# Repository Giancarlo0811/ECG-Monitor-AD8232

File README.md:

# ECG-Monitor-AD8232
Diseño de Monitor ECG (Electrocardiograma) de una sola derivación (Single Lead) basado en el AFE TI AD8232.

## 📚 Proyecto Académico
*Proyecto desarrollado como parte de la asignatura ***EC3083 Taller de Equipos Electrónicos*** en la Universidad Simón Bolívar.*

**Objetivo**: Diseñar un circuito ECG con esquemático y PCB layout.

## 🛠️ Detalles Técnicos
- **Herramientas**:
    - **Proteus**: Esquemático, simulación y PCB.
    - **KiCad**: Esquemático y PCB.
- **Características clave**:
    - **Analog Front End (AFE)**: TI AD8232.
    - **Acondicionamiento de señal**: filtro pasabanda 0.445-43.6 Hz (simulado en Proteus).
    - **Ganancia media banda**: 59.1 dB (simulado en Proteus).
    - **Diseño PCB**: 2-layer layout.
    - **Bill of Materials (BOM)**: Lista de componentes completa con costos.

## 📸 Esquemático + PCB

### Proteus

### KiCad

## 📊 Simulación

### 📈 Bode de amplitud y fase de la ganancia modo diferencial

Caso pasa bajo: fc = 43.6 Hz

Caso pasa alto: fc = 0.445 Hz

Avd = 59,1 dB frecuencias medias

### 📈 Vid (ECG simulado 0.625 mVp) y Vo (OUT)

## 📋 BOM (Bill of Materials)
[Descargar BOM](./Documentos/BOM_Monitor_ECG_AFE_AD8232.xlsx)

## 📂 Documentación completa
Para una documentación más detallada descargar:
[Presentación PDF](/Documentos/Presentacion_ECG_Monitor_AFE_AD8232.pdf)

## ⚠️ Disclaimer
Esto es un diseño teórico. La fabricación de la PCB y sus pruebas están pendientes.

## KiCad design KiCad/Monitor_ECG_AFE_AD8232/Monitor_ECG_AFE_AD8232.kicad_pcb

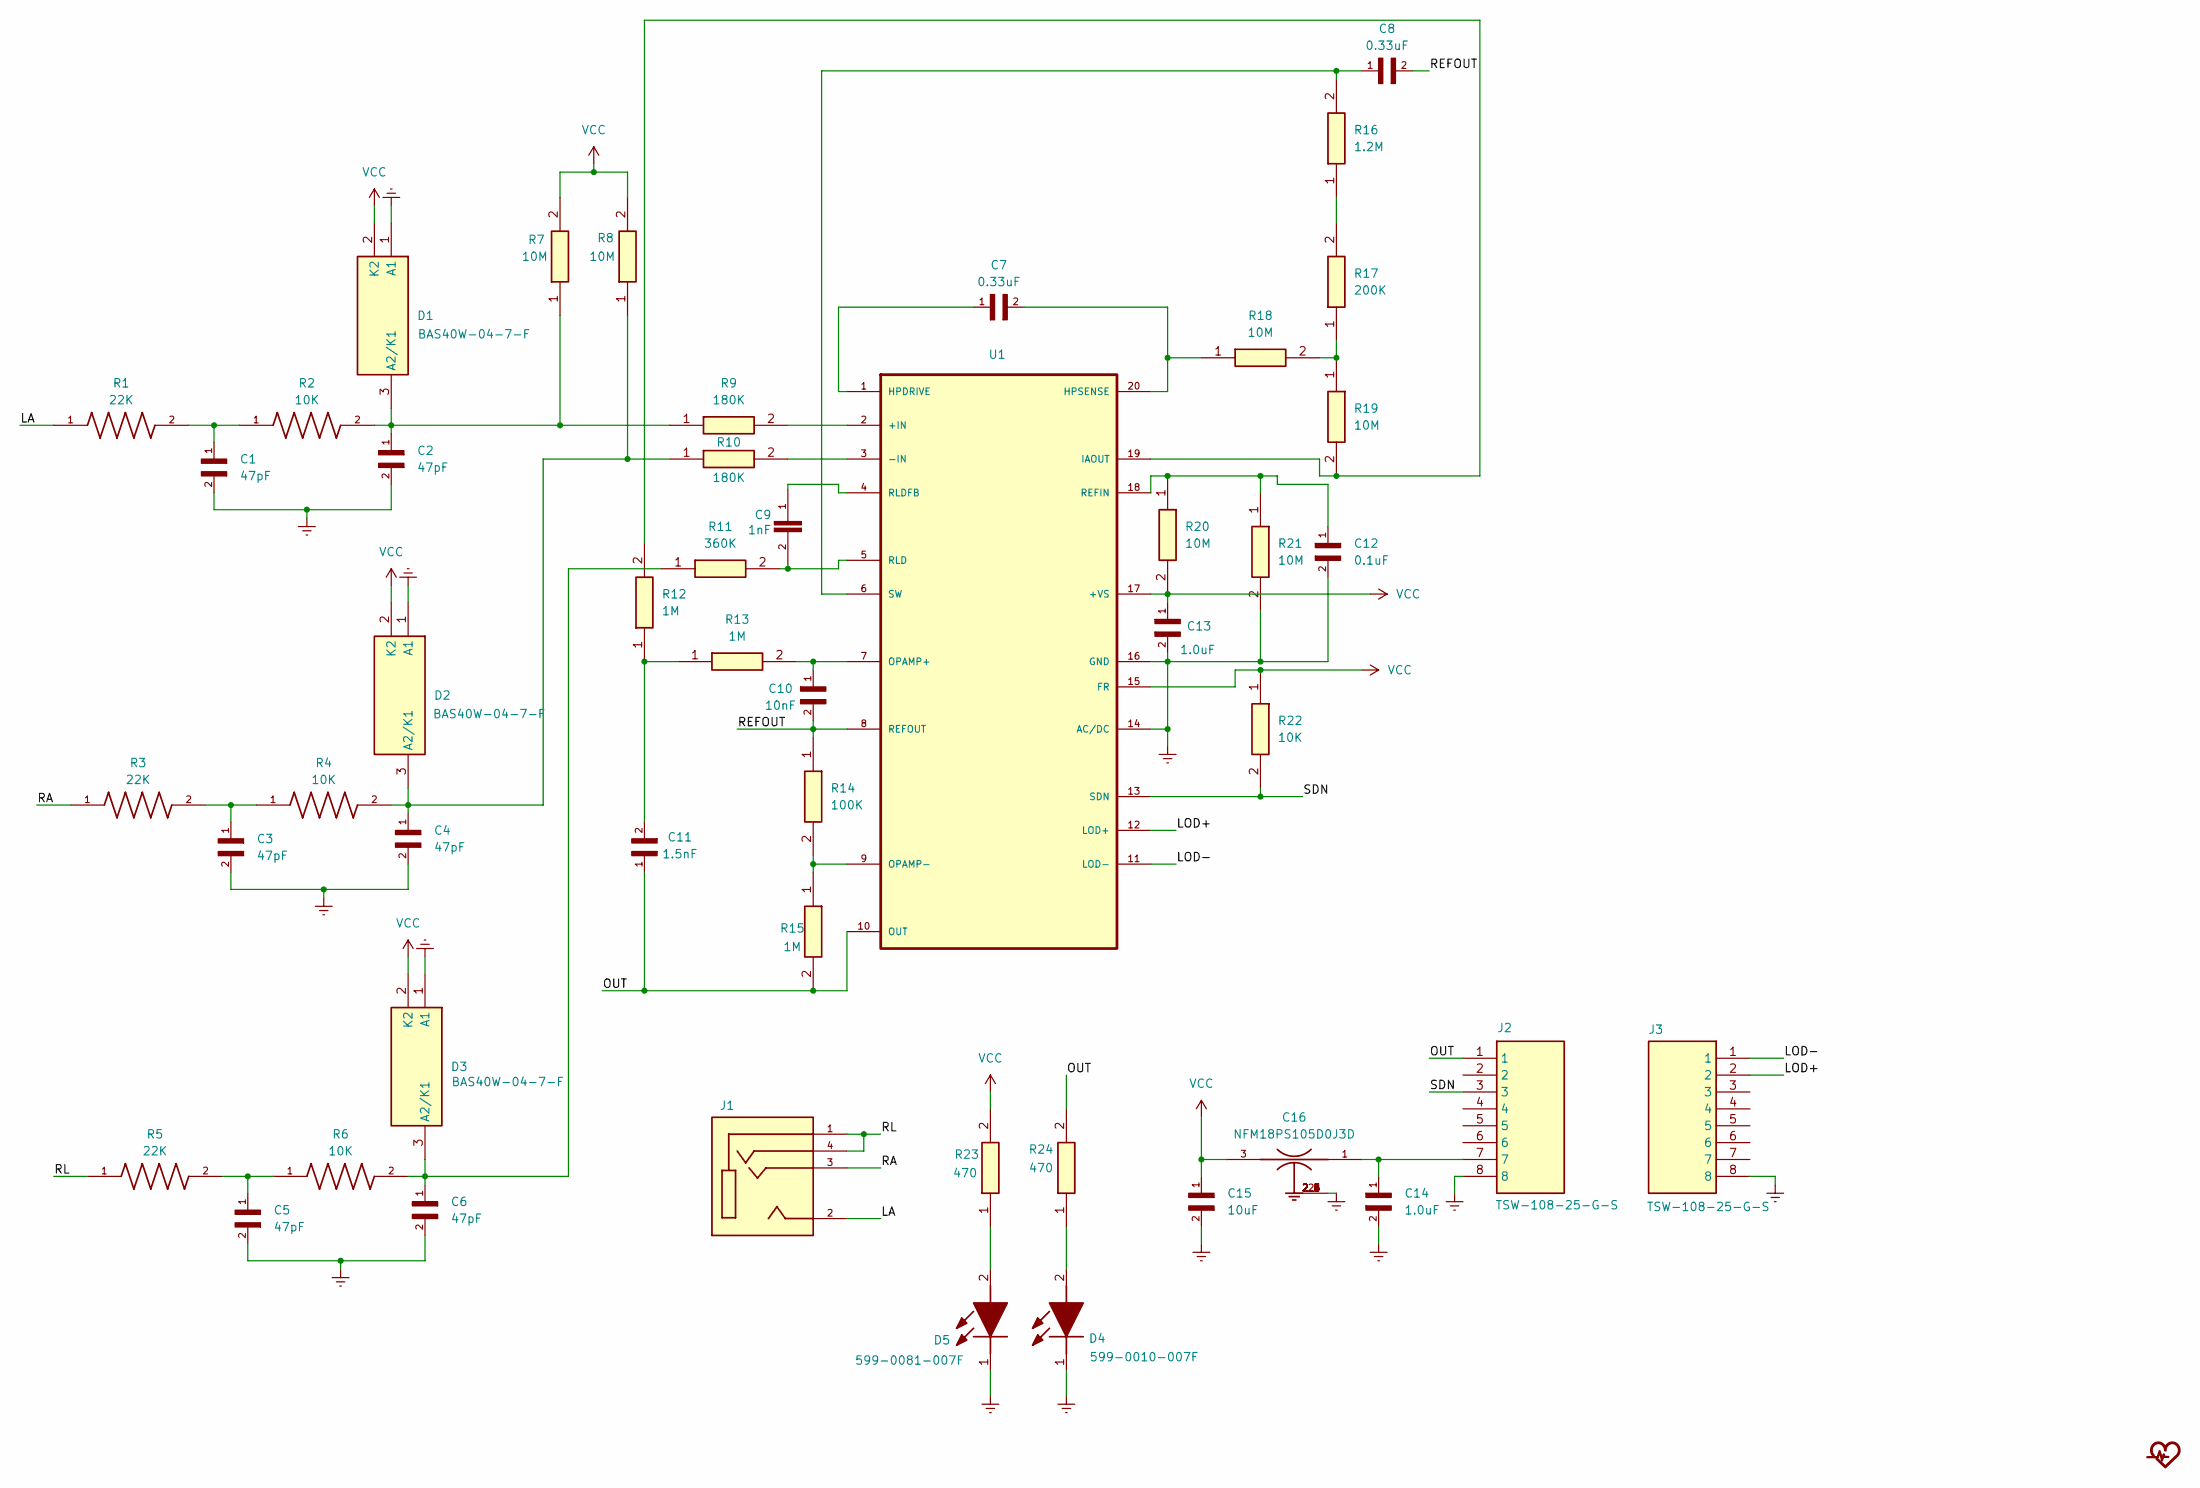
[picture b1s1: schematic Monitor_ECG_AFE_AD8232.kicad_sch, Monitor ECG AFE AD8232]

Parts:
C1, C2, C3, C4, C5, C6: 47pF; CAPC1608X90
C7, C8: 0.33uF; CAPC1608X87N
C9: 1nF; CAPC1608X90
C10: 10nF; CAPC1608X90
C11: 1.5nF; CAPC1608X90
C12: 0.1uF; CAPC1608X90N
C13, C14: 1.0uF; CAPC1608X90N
C15: 10uF; CAPC1608X90N
C16: NFM18PS105D0J3D; FIL_NFM18PS105D0J3D
D1, D2, D3: BAS40W-04-7-F; SOT65P222X110-3N; Manufacturer_Part_Number BAS40W-04-7-F; Mouser Part Number 621-BAS40W-04-F
D4: 599-0010-007F; LEDM168X70N; Manufacturer_Part_Number 599-0010-007F; Mouser Part Number 645-599-0010-007F
D5: 599-0081-007F; CAPC1608X95; Manufacturer_Part_Number 599-0081-007F; Mouser Part Number 645-599-0081-007F
ECG_logo1: LOGO; logo_5x5
J1: SJ-43514-SMT-TR; CUI_SJ-43514-SMT-TR; PARTREV 1.05
J2, J3: TSW-108-25-G-S; TSW-108-XX-YY-S; Manufacturer_Part_Number TSW-108-25-G-S; Mouser Part Number 200-TSW10825GS
R1, R3, R5: 22K; RESC1608X55N
R2, R4, R6: 10K; RES_ERJ-3GEYJ103V; PARTREV 3/1/2020
R7, R8, R18, R19, R20, R21: 10M; RESC1608X55N; Manufacturer_Part_Number ERJ-3GEYJ106V; Mouser Part Number 667-ERJ-3GEYJ106V
R9, R10: 180K; RESC1608X55N; Manufacturer_Part_Number RC0603JR-07180KL; Mouser Part Number 603-RC0603JR-07180KL
R11: 360K; RESC1608X55N; Manufacturer_Part_Number RC0603FR-07360KL; Mouser Part Number 603-RC0603FR-07360KL
R12, R13, R15: 1M; RESC1608X55N; Manufacturer_Part_Number ERJ-3GEYJ105V; Mouser Part Number 667-ERJ-3GEYJ105V
R14: 100K; RESC1608X55N; Manufacturer_Part_Number ERJ-3EKF1003V; Mouser Part Number 667-ERJ-3EKF1003V
R16: 1.2M; RESC1608X55N; Manufacturer_Part_Number ERJ-3GEYJ125V; Mouser Part Number 667-ERJ-3GEYJ125V
R17: 200K; RESC1608X55N; Manufacturer_Part_Number RC0603JR-07200KL; Mouser Part Number 603-RC0603JR-07200KL
R22: 10K; RESC1608X55N; Manufacturer_Part_Number ERJ-3EKF1002V; Mouser Part Number 667-ERJ-3EKF1002V
R23, R24: 470; RESC1608X55N; Manufacturer_Part_Number RC0603JR-07470RL; Mouser Part Number 603-RC0603JR-07470RL
U1: AD8232ACPZ-R7; QFN50P400X400X100-21N

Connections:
/LA: J1.2, R1.1
/LOD+: J3.2, U1.12 (LOD+)
/LOD-: J3.1, U1.11 (LOD-)
/OUT: C11.1, J2.1, R15.2, R24.2, U1.10 (OUT)
/RA: J1.3, R3.1
/REFOUT: C8.2, C10.2, R14.1, U1.8 (REFOUT)
/RL: J1.1, J1.4, R5.1
/SDN: J2.3, R22.2, U1.13 (SDN)
Earth: C1.2, C2.2, C3.2, C4.2, C5.2, C6.2, C12.2, C13.2, C14.2, C15.2, C16.2, C16.2_1, C16.2_2, C16.2_3, C16.2_4, C16.2_5, C16.2_6, D1.1 (A1), D2.1 (A1), D3.1 (A1), D4.1 (K), D5.1 (K), J2.8, J3.8, R21.2, U1.14 (AC/DC), U1.16 (GND)
unnamed: C1.1, R1.2, R2.1
unnamed: C3.1, R3.2, R4.1
unnamed: C5.1, R5.2, R6.1
unnamed: C11.2, R12.1, R13.1
unnamed: C14.1, C16.1, J2.7
unnamed: C2.1, D1.3 (A2/K1), R2.2, R7.1, R9.1
unnamed: C4.1, D2.3 (A2/K1), R4.2, R8.1, R10.1
unnamed: C6.1, D3.3 (A2/K1), R6.2, R11.1
unnamed: D4.2 (A), R24.1
unnamed: D5.2 (A), R23.1
unnamed: R16.1, R17.2
unnamed: R17.1, R18.2, R19.1
unnamed: R9.2, U1.2 (+IN)
unnamed: R10.2, U1.3 (-IN)
unnamed: C7.1, U1.1 (HPDRIVE)
unnamed: C7.2, R18.1, U1.20 (HPSENSE)
unnamed: R12.2, R19.2, U1.19 (IAOUT)
unnamed: C10.1, R13.2, U1.7 (OPAMP+)
unnamed: R14.2, R15.1, U1.9 (OPAMP-)
unnamed: C12.1, R20.1, R21.1, U1.18 (REFIN)
unnamed: C9.2, R11.2, U1.5 (RLD)
unnamed: C9.1, U1.4 (RLDFB)
unnamed: C8.1, R16.2, U1.6 (SW)
VCC: C13.1, C15.1, C16.3, D1.2 (K2), D2.2 (K2), D3.2 (K2), R7.2, R8.2, R20.2, R22.1, R23.2, U1.15 (FR), U1.17 (+VS)

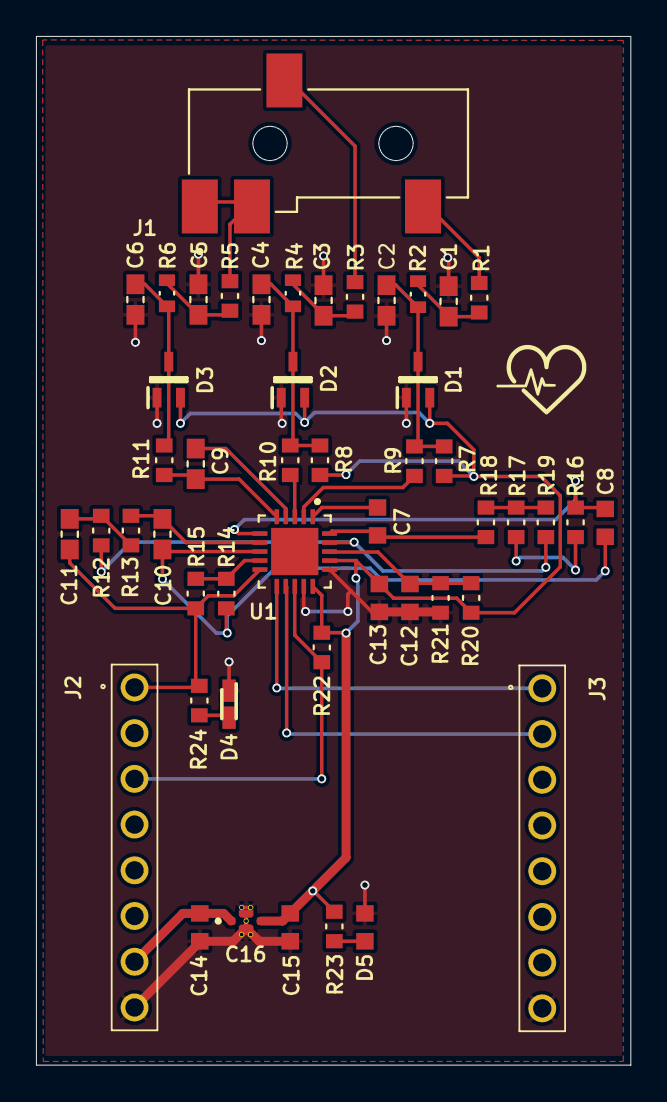
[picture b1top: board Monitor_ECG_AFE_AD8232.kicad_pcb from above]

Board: 2 copper layers, 33.0 x 57.2 mm, 50 parts (0 on the bottom side), 33 nets.

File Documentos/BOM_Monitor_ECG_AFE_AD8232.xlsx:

Bill Of Materials for Monitor ECG AFE AD8232
Design Title |  |  | Monitor ECG AFE AD8232
Author |  |  | Giancarlo Torlone
Document Number |  |  | 2
Revision |  |  | 2
Design Created |  |  | jueves, 15 de mayo de 2025
Design Last Modified |  |  | jueves, 15 de mayo de 2025
Total Parts In Design |  |  | 49
 |  |  |  |  |  |  |  |  |  |  | Totals
Category | Quantity | References | Value | Stock Code | Unit Cost | Manufacturer | Description | PCB Package | Manufacture Part Number |  | Category | Quantity | Unit Cost
Capacitors | 6 | C1-C6 | 47pF | Digikey 311-1065-1-ND | $0,10 | Yageo | CAP CERAMIC 47pF 50V NP0 0603 | CAPC1608X87 | CC0603JRNPO9BN470 |  | Modules | 0 | $0,00
Capacitors | 2 | C7-C8 | 0.33u | Digikey 399-4918-2-ND | $0,46 | Kemet | CAP CERM .33uF 6.3V X7R 0603 | CAPC1608X87 | C0603C334K9RACTU |  | Capacitors | 16 | $2,60
Capacitors | 1 | C9 | 1nF | Digikey 311-1080-1-ND | $0,10 | Yageo | CAP 1000pF 50V CERAMIC X7R 0603 | CAPC1608X87 | CC0603KRX7R9BB102 |  | Resistors | 24 | $2,40
Capacitors | 1 | C10 | 10nF | Digikey 311-1085-2-ND | $0,10 | Yageo | CAP 10000pF 50V CERAMIC X7R 0603 | CAPC1608X87 | CC0603KRX7R9BB103 |  | Integrated Circuits | 1 | $3,82
Capacitors | 1 | C11 | 1.5nF | Digikey 311-1184-6-ND | $0,10 | Yageo | CAP 1500pF 50V CERAMIC X7R 0603 | CAPC1608X87 | CC0603KRX7R9BB152 |  | Transistors | 0 | $0,00
Capacitors | 1 | C12 | 0.1u | Digikey 478-1239-1-ND | $0,12 | AVX | CAP CERM .1uF 10% 16V X7R 0603 | CAPC1608X87 | 0603YC104KAT2A |  | Diodes | 5 | $2,00
Capacitors | 2 | C13-C14 | 1.0u | Digikey 399-3217-1-ND | $0,12 | Kemet | CAP 1uF 6.3V CER Y5V SMD 0603 | CAPC1608X87 | C0603C105Z9VACTU |  | Miscellaneous | 3 | $3,86
Capacitors | 1 | C15 | 10u | Digikey 399-5504-1-ND | $0,32 | KEMET | CAPACITOR, 0603 10uF +/-20% 6.3V | CAPC1608X87 | C0603C106M9PACTU |  | Total | 49 | $14,68
Capacitors | 1 | C16 | NFM18PS105D0J3D | Digikey 490-13394-2-ND | $0,10 | Murata Electronics | 1F Feed Through Capacitor 6.3V 2A 30mOhm 0603 (1608 Metric), 3 PC Pad | NFM18CC101R1C3D | NFM18PS105D0J3D
Resistors | 3 | R1,R3,R5 | 22K | Digikey 311-22KGRCT-ND | $0,10 | Yageo | RES 22K OHM 1/10W 5% 0603 (1608 metric) SMD | RESC1608X50A | RC0603JR-0722KL
Resistors | 3 | R2,R4,R6 | 10K | Digikey P10KGCT-ND | $0,10 | Panasonic - ECG | RES 10K OHM 1/10W 5% 0603 (1608 metric) SMD | RESC1608X50A | ERJ-3GEYJ103V
Resistors | 6 | R7-R8,R18-R21 | 10M | Digikey P10MGCT-ND | $0,10 | Yageo | RESISTOR, 0603 10M Ohms +/-5% 1/10 W | RESC1608X50A | ERJ-3GEYJ106V
Resistors | 2 | R9-R10 | 180K | Digikey 311-180KGRCT-ND | $0,10 | Yageo | RESISTOR, 0603 180K Ohms +/-5% 1/10 W | RESC1608X50A | RC0603JR-07180KL
Resistors | 1 | R11 | 360K | Digikey 311-360KHRCT-ND | $0,10 | Yageo | RESISTOR, 0603 360K Ohms +/-5% 1/10 W | RESC1608X50A | RC0603FR-07360KL
Resistors | 3 | R12-R13,R15 | 1M | Digikey P1.0MGCT-ND | $0,10 | Panasonic - ECG | RES 1.0M OHM 1/10W 5% 0603 (1608 metric) SMD | RESC1608X50A | ERJ-3GEYJ105V
Resistors | 1 | R14 | 100K | Digikey P100KHTR-ND | $0,10 | Panasonic - ECG | RES 100K OHM 1/10W 1% 0603 (1608 metric) SMD | RESC1608X50A | ERJ-3EKF1003V
Resistors | 1 | R16 | 1.2M | Digikey P1.2MGCT-ND | $0,10 | Panasonic - ECG | RES 1.2M OHM 1/10W 5% 0603 (1608 metric) SMD | RESC1608X50A | ERJ-3GEYJ125V
Resistors | 1 | R17 | 200K | Digikey 311-200KGRCT-ND | $0,10 | Yageo | RESISTOR, 0603 200K Ohms +/-5% 1/10 W | RESC1608X50A | RC0603JR-07200KL
Resistors | 1 | R22 | 10.0K | Digikey P10.0KHTR-ND | $0,10 | Panasonic - ECG | RES 10.0K OHM 1/10W 1% 0603 (1608 metric) SMD | RESC1608X50A | ERJ-3EKF1002V
Resistors | 2 | R23-R24 | 470 | Digikey 311-470GRCT-ND | $0,10 | Yageo | RESISTOR, 0603 470 Ohms +/-5% 1/10 W | RESC1608X50A | RC0603JR-07470RL
Integrated Circuits | 1 | U1 | AD8232ACPZ-R7-2 | AD8232ACPZ-R7TR-ND | $3,82 | Analog Devices | ANALOG DEVICES - ADACPZ-R7 - SIGNAL CONDITIO | QFN50P400X400X80-21 | AD8232ACPZ-R7
Diodes | 3 | D1-D3 | BAS40W-04 | Digikey BAS40W-04FDICT-ND | $0,34 | Diodes Inc. | Schottky - 40.0V 0.200A 5.00ns | SOT23-D9 | BAS40W-04-7-F
Diodes | 1 | D4 | 599-0010-007F | Digikey 350-4346-1-ND | $0,37 | Dialight | Standard LEDs - SMD SMD 0603 RED | LEDC1608X90N | 5990010007F
Diodes | 1 | D5 | 599-0081-007F | Digikey 350-4351-1-ND | $0,61 | Dialight | Standard LEDs - SMD SMD 0603 GREEN | LEDC1608X90N | 5990081007F
Miscellaneous | 1 | J1 | SJ-43514-SMT-TR | Digikey CP-43514SJCT-ND | $1,06 | CUI Devices | Phone Connectors Audio Jacks | SJ43514SMTTR | SJ-43514-SMT-TR
Miscellaneous | 2 | J2-J3 | TSW-108-25-G-S | Digikey TSW-108-25-G-S-ND | $1,40 | Samtec Inc. | 8 Position, Single Row, Classic PCB Header Strips, 0.100&quot; pitch | TSW-108-XX-YY-S | TSW-108-25-G-S

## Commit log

2025-05-13 ECG monitor
2025-05-13 readme actualizado
2025-05-14 imagen borrada
2025-05-15 simulacion ECG
2025-05-15 archivo proteus simulacion subido
2025-05-17 archivos actualizados
2025-05-18 esquematico modificado
2025-05-18 proteus pcb y gerbers
2025-05-29 version KiCad agregada
2025-05-30 version kicad cambiada
2025-05-30 version kicad modificada
